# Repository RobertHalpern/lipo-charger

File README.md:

# lipo-charger
Lithium Polymer battery charger using TP4057 integrated circuit.

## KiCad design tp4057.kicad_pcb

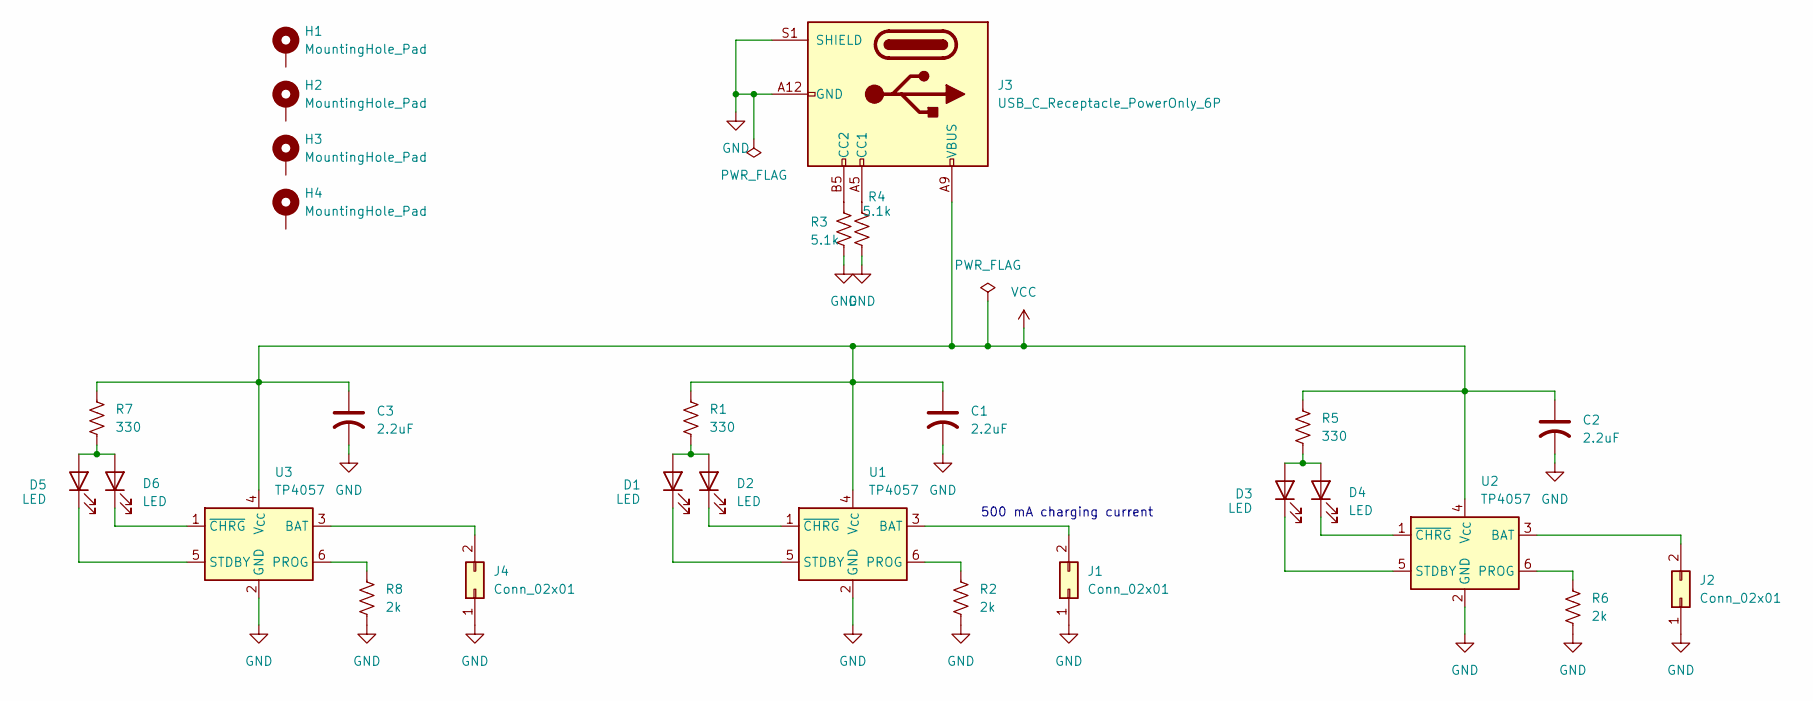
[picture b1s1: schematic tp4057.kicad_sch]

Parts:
C1, C2, C3: 2.2uF; C_0603_2012Metric
D1, D2, D3, D4, D5, D6: LED; LED_0805_2012Metric_Pad1.15x1.40mm_HandSolder
H1, H2, H3, H4: MountingHole_Pad; MountingHole_2.2mm_M2_Pad
J1, J2, J4: Conn_02x01; JST_PH_B2B-PH-SM4-TB_1x02-1MP_P2.00mm_Vertical
J3: USB_C_Receptacle_PowerOnly_6P; USB_C_Receptacle_GCT_USB4125-xx-x_6P_TopMnt_Horizontal
R1, R5, R7: 330; R_0805_2012Metric_Pad1.20x1.40mm_HandSolder
R2, R6, R8: 2k; R_0805_2012Metric_Pad1.20x1.40mm_HandSolder
R3, R4: 5.1k; R_0805_2012Metric_Pad1.20x1.40mm_HandSolder
U1, U2, U3: TP4057; TSOT-23-6

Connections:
GND: C1.2, C2.2, C3.2, J1.1, J2.1, J3.A12 (GND), J3.B12 (GND), J3.S1 (SHIELD), J4.1, R2.2, R3.2, R4.2, R6.2, R8.2, U1.2 (GND), U2.2 (GND), U3.2 (GND)
unnamed: D1.2 (A), D2.2 (A), R1.2
unnamed: D1.1 (K), U1.5 (STDBY)
unnamed: D2.1 (K), U1.1 (~CHRG)
unnamed: D3.2 (A), D4.2 (A), R5.2
unnamed: D3.1 (K), U2.5 (STDBY)
unnamed: D4.1 (K), U2.1 (~CHRG)
unnamed: D5.2 (A), D6.2 (A), R7.2
unnamed: D5.1 (K), U3.5 (STDBY)
unnamed: D6.1 (K), U3.1 (~CHRG)
unnamed: J1.2, U1.3 (BAT)
unnamed: J2.2, U2.3 (BAT)
unnamed: J3.A5 (CC1), R4.1
unnamed: J3.B5 (CC2), R3.1
unnamed: J4.2, U3.3 (BAT)
unnamed: R2.1, U1.6 (PROG)
unnamed: R6.1, U2.6 (PROG)
unnamed: R8.1, U3.6 (PROG)
VCC: C1.1, C2.1, C3.1, J3.A9 (VBUS), J3.B9 (VBUS), R1.1, R5.1, R7.1, U1.4 (V_{CC}), U2.4 (V_{CC}), U3.4 (V_{CC})

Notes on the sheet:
500 mA charging current

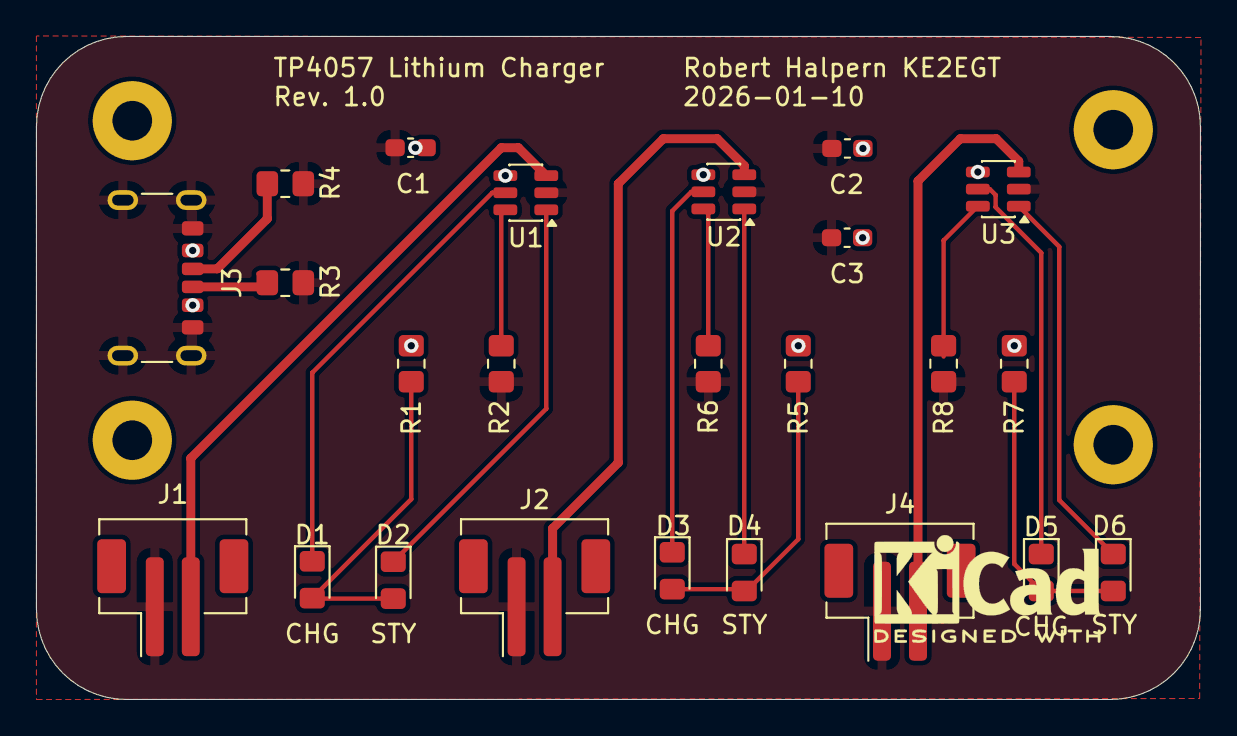
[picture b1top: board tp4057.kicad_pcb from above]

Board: 2 copper layers, 64.7 x 36.8 mm, 28 parts (0 on the bottom side), 19 nets.

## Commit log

2026-01-04 Initial KiCad project
2026-01-07 Fixed VCC plane not connecting (misplaced vias), changed trace thickness, routed remaining components
2026-01-11 Board layout; new 3D JST footprint; added silkscreen
